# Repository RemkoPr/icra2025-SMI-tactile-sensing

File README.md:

# ICRA2025: Self-Mixing Laser Interferometry for Robotic Tactile Sensing

[[Main Paper](https://arxiv.org/abs/2502.15390), [Follow-up](https://arxiv.org/abs/2504.13711)] The source files in this repo are provided as-is, additional support for recreating the design can be requested, see contact information below.

# Repo structure

`code > arduino` contains readout firmware for the fingertips. In the paper, the SMI fingertip was read by an Arduino UNO or our [Halberd coupling](https://github.com/RemkoPr/airo-halberd/tree/main), the microphone was read by an Arduino MKR 1000 WiFi.

`code > python` contains code to communicate with the readout microcontrollers from a remote machine over a serial connection.

`data` contains the data files used in the paper.

`mechanical-design` contains SolidWorks design files for the structural parts of the fingertips.

`pcb-design` contains KiCad design files for the PCBs.

For the spectrogram classificatier used in the [follow-up paper](https://arxiv.org/abs/2504.13711), see [this repo](https://github.com/tlpss/ast).

# User Guide

The info in this paragraph is relevant for both the microphone and the laser.

Order the PCBs (`pcb-design > microphone` and `pcb-design > laser`) from your favorite manufacturer, refer to the BOM in the main directory of this repo for required parts.
Print the .stl files in `mechanical-design`.
The process of moulding the silicone contact surface is illustrated by the graphic on the right. To keep the "sensor cavity insert" in the right position, fix it with hot glue. It is recommended to attach the "mounting interface" to the fingertip while curing, so that the silicone has less chance to leak.

<BR CLEAR="all">

## Microphone specifics

On the PCB, you must set the microphone to either by left or right channel, this will determine during which phase of the I2S communication cycle the microphone sends its data. Do this by soldering a bridge as indicated on the image (the readout code in this repo was tested for left channel, so with a bridge soldered from the middle pad to the L pad).

The MKR1000 firmware (`code > arduino > microphone`) was used for the paper, the wiring is explained in the top rows of the `I2S_MKR1000.ino` file. The `I2S_ArduinoNanoBLE_16kHz` is a first attempt at a readout implementation for the Arduino Nano 33 BLE, for which the standard I2S library isn't implemented.

To run the Python code (`code > python`), run `python -m code.python.communication.readers.micmanip_serial_reader`. The data is published to a CycloneDDS topic MicManip. You can visualise it using `python -m code.python.visualisation.visualisers.micmanip_spectrogram_visualiser MicManip`
<BR CLEAR="all">

## Laser specifics

⚠️ The SMI circuit has a ~5 min warmup time before microvibrations can be measured.

The readout frequency when read with an Arduino UNO was 3.7kHz, and 18kHz with our [Halberd coupling](https://github.com/RemkoPr/airo-halberd/tree/main) (or equivalently with an Arduino Nano 33 BLE, same microcontroller unit). When using higher readout frequency, turn off the 2kHz anti-aliasing filter with the on-PCB slide switch.

To run the Python code (`code > python`), run `python -m code.python.communication.readers.laserslip_serial_reader`. The data is published to a CycloneDDS topic LaserSlip. You can visualise it using `python -m code.python.visualisation.visualisers.laserslip_spectrogram_visualiser LaserSlip`

# Contact

For support regarding the design files in this repo, raise an issue or contact me at remko.proesmans@ugent.be.

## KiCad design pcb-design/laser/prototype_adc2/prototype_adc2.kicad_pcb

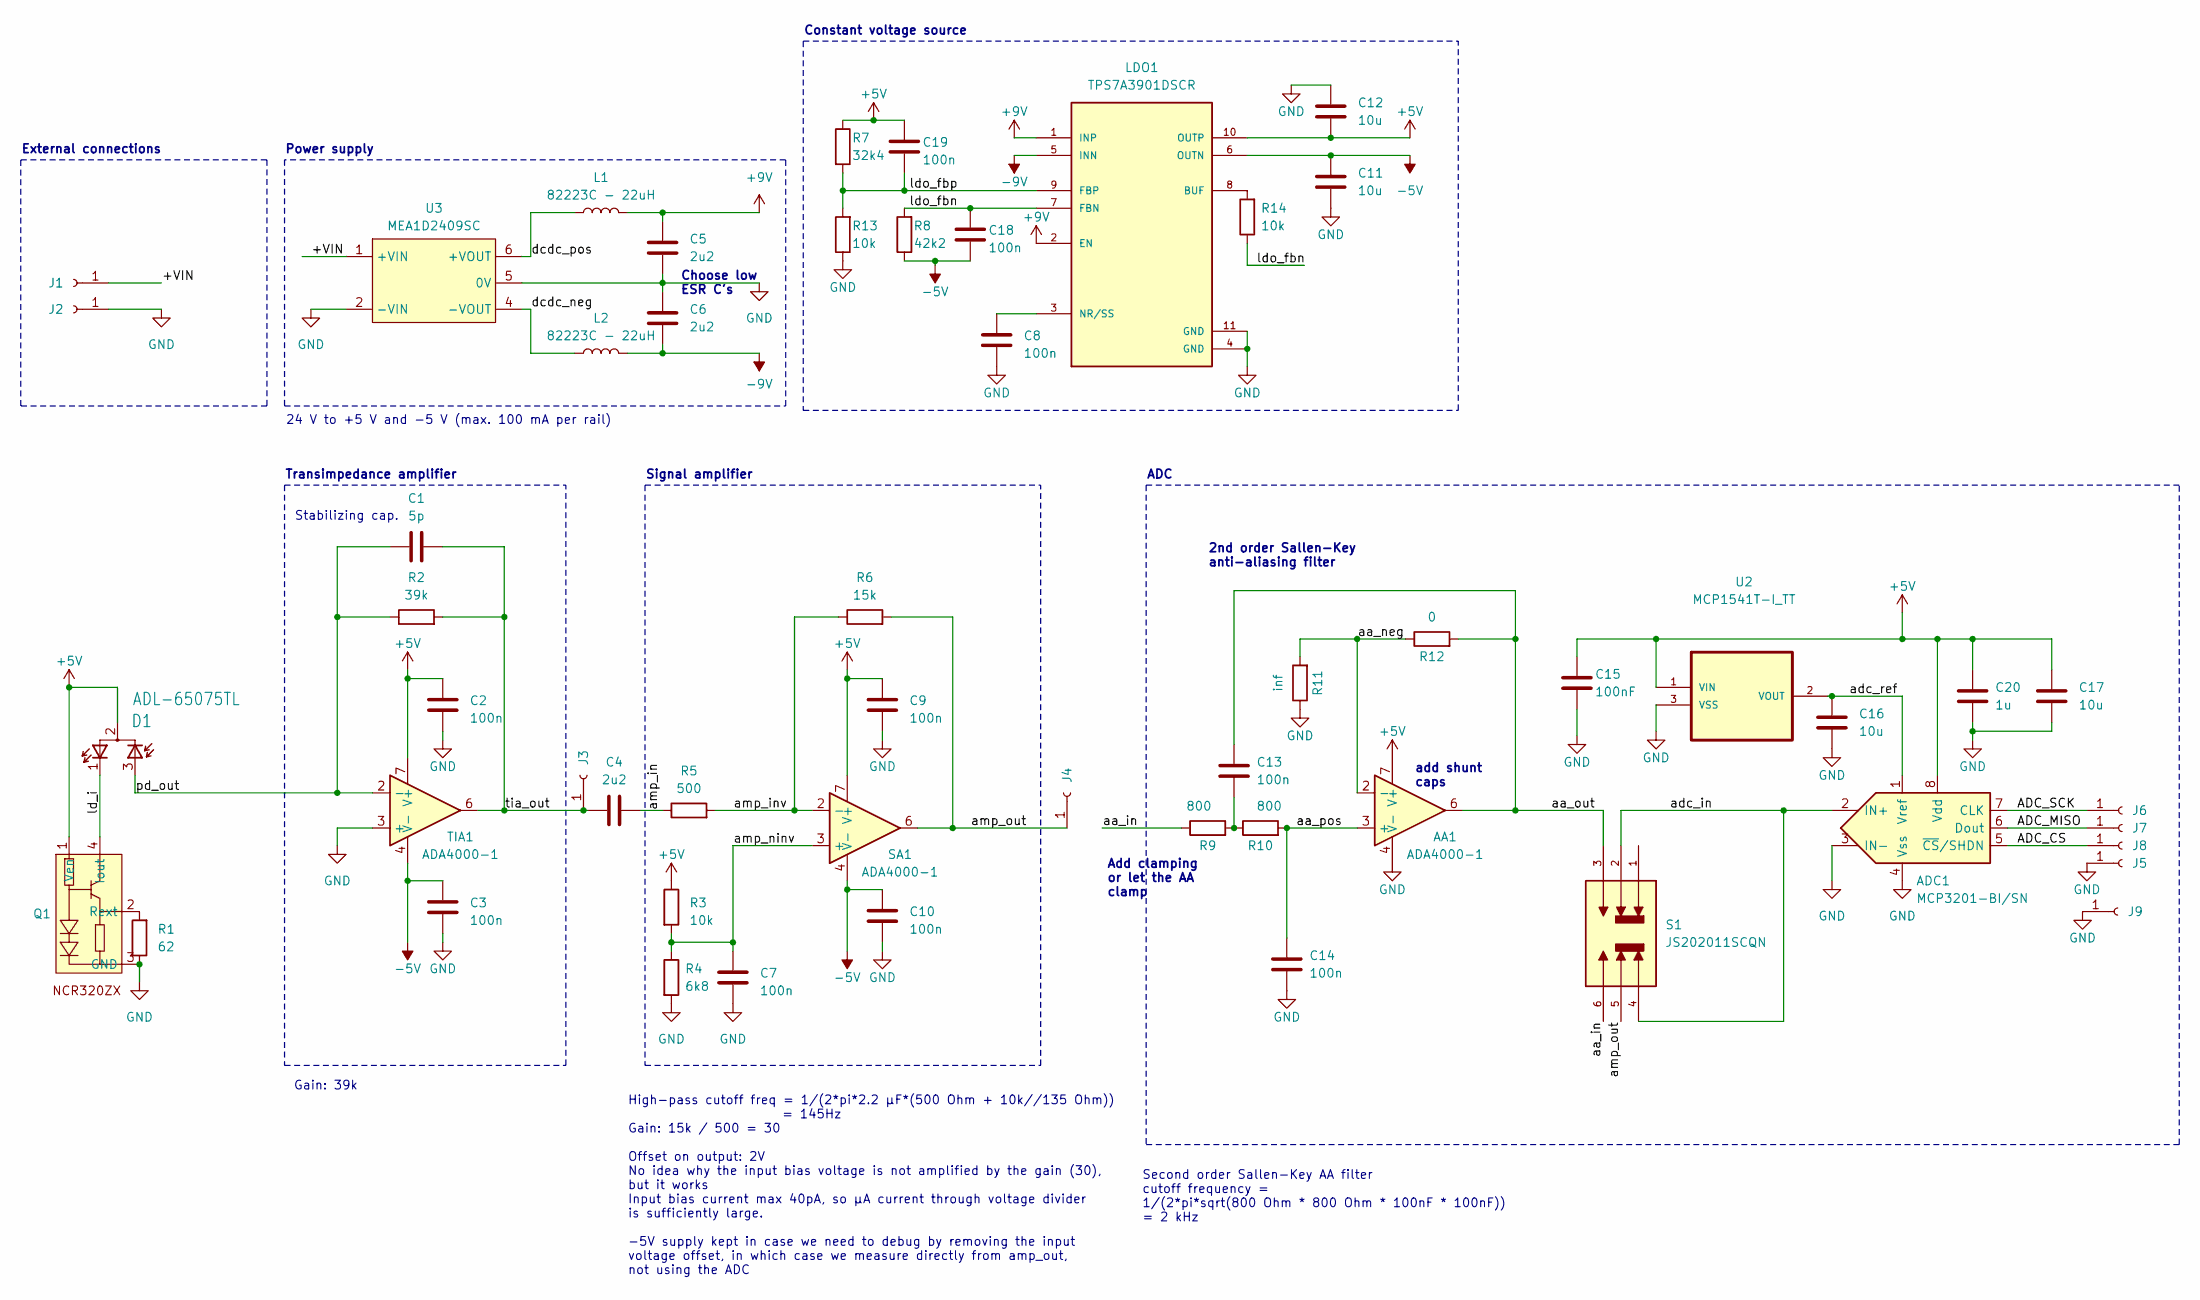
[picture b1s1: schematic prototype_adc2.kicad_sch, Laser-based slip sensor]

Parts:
AA1: ADA4000-1; ada4000-SOIC127P600X175-8N
ADC1: MCP3201-BI/SN; SOIC127P600X175-8N
C1: 5p; C_0603_1608Metric
C2, C3, C7, C8, C9, C10, C13, C14, C18, C19: 100n; C_0603_1608Metric
C4, C5, C6: 2u2; C_0603_1608Metric
C11, C12, C16, C17: 10u; C_0603_1608Metric
C15: 100nF; C_0603_1608Metric
C20: 1u; C_0603_1608Metric
D1: ADL-65075TL; TO18L
J1, J2, J3, J4, J5, J6, J7, J8, J9: Conn_01x01_Socket; HOLE
L1, L2: 82223C - 22uH; 8200
LDO1: TPS7A3901DSCR; SON50P300X300X80-11N
Q1: TRANS_BCP56-16TX
R1: 62; R_0603_1608Metric
R2: 39k; R_0603_1608Metric
R3, R13, R14: 10k; R_0603_1608Metric
R4: 6k8; R_0603_1608Metric
R5: 500; R_0603_1608Metric
R6: 15k; R_0603_1608Metric
R7: 32k4; R_0603_1608Metric
R8: 42k2; R_0603_1608Metric
R9, R10: 800; R_0603_1608Metric
R11: inf; R_0603_1608Metric
R12: 0; R_0603_1608Metric
S1: JS202011SCQN; SW_JS202011SCQN
SA1: ADA4000-1; ada4000-SOIC127P600X175-8N
TIA1: ADA4000-1; ada4000-SOIC127P600X175-8N
U2: MCP1541T-I_TT; SOT96P237X112-3N
U3: MEA1D2409SC

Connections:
+5V: AA1.7 (V+), ADC1.8 (Vdd), C2.1, C9.1, C12.2, C15.1, C17.1, C19.1, C20.1, D1.2 (CMONI), LDO1.10 (OUTP), Q1.1 (Ven), R3.1, R7.1, SA1.7 (V+), TIA1.7 (V+), U2.1 (VIN)
+9V: C5.1, L1.2, LDO1.1 (INP), LDO1.2 (EN)
-5V: C3.1, C10.1, C11.1, C18.2, LDO1.6 (OUTN), R8.1, SA1.4 (V-), TIA1.4 (V-)
-9V: C6.2, L2.2, LDO1.5 (INN)
/+VIN: J1.1, U3.1 (+VIN)
/ADC_CS: ADC1.5 (~CS/SHDN), J8.1
/ADC_MISO: ADC1.6 (Dout), J7.1
/ADC_SCK: ADC1.7 (CLK), J6.1
/aa_in: R9.1, S1.6
/aa_neg: AA1.2 (-), R11.2, R12.1
/aa_out: AA1.6, C13.1, R12.2, S1.3
/aa_pos: AA1.3 (+), C14.1, R10.2
/adc_in: ADC1.2 (IN+), S1.2, S1.4
/adc_ref: ADC1.1 (Vref), C16.1, U2.2 (VOUT)
/amp_in: C4.2, R5.1
/amp_inv: R5.2, R6.1, SA1.2 (-)
/amp_ninv: C7.1, R3.2, R4.1, SA1.3 (+)
/amp_out: J4.1, R6.2, S1.5, SA1.6
/dcdc_neg: L2.1, U3.4 (-VOUT)
/dcdc_pos: L1.1, U3.6 (+VOUT)
/ld_i: D1.1 (C), Q1.4 (Iout)
/ldo_fbn: C18.1, LDO1.7 (FBN), R8.2, R14.1
/ldo_fbp: C19.2, LDO1.9 (FBP), R7.2, R13.2
/pd_out: C1.1, D1.3 (A), R2.1, TIA1.2 (-)
/tia_out: C1.2, C4.1, J3.1, R2.2, TIA1.6
GND: AA1.4 (V-), ADC1.3 (IN-), ADC1.4 (Vss), C2.2, C3.2, C5.2, C6.1, C7.2, C8.2, C9.2, C10.2, C11.2, C12.1, C14.2, C15.2, C16.2, C17.2, C20.2, J2.1, J5.1, J9.1, LDO1.4 (GND), LDO1.11 (GND), Q1.3 (GND), R1.1, R4.2, R11.1, R13.1, TIA1.3 (+), U2.3 (VSS), U3.2 (-VIN), U3.5 (0V)
unnamed: C13.2, R9.2, R10.1
unnamed: LDO1.8 (BUF), R14.2
unnamed: C8.1, LDO1.3 (NR/SS)
unnamed: Q1.2 (Rext), R1.2

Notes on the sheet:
ADC
Add clamping or let the AA clamp
Second order Sallen-Key AA filter cutoff frequency = 1/(2*pi*sqrt(800 Ohm * 800 Ohm * 100nF * 100nF)) = 2 kHz
2nd order Sallen-Key anti-aliasing filter
High-pass cutoff freq = 1/(2*pi*2.2 µF*(500 Ohm + 10k//135 Ohm)) = 145Hz Gain: 15k / 500 = 30 Offset on output: 2V No idea why the input bias voltage is not amplified by the gain (30), but it works Input bias current max 40pA, so µA current through voltage divider is sufficiently large. -5V supply 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
Gain: 39k
24 V to +5 V and -5 V (max. 100 mA per rail)
Stabilizing cap.
External connections
Signal amplifier
Transimpedance amplifier
add shunt caps
Constant voltage source
Power supply
Choose low ESR C's

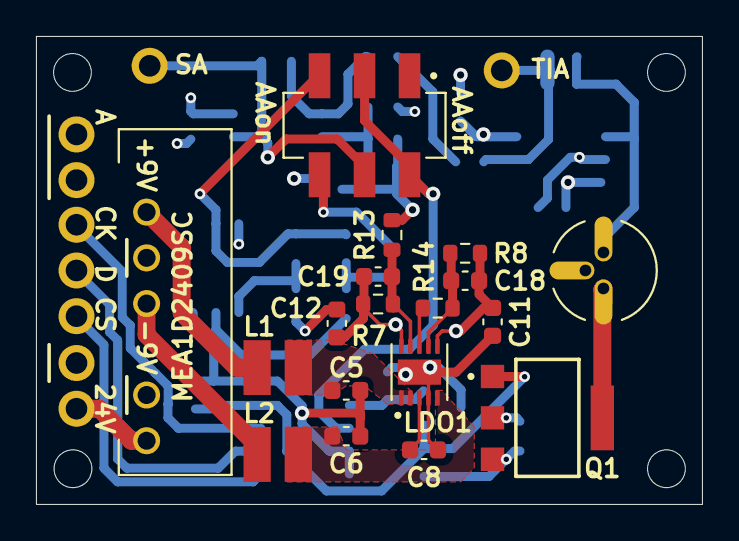
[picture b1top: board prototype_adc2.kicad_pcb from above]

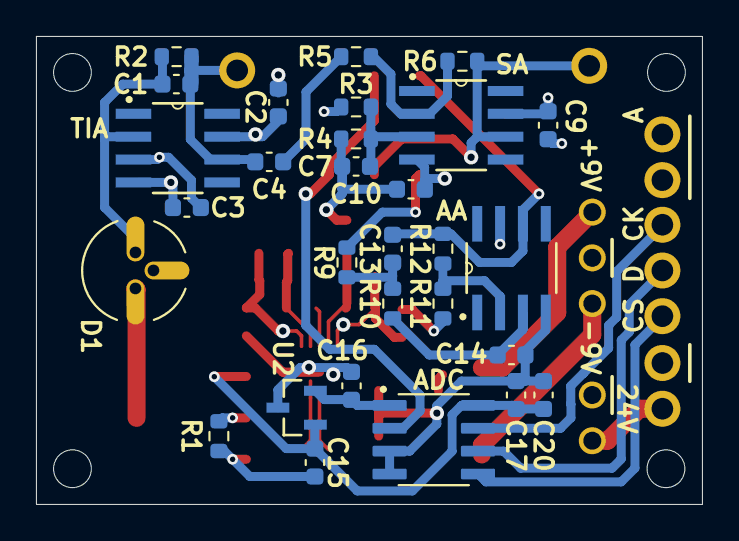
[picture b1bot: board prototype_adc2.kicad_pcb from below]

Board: 4 copper layers, 37.0 x 26.0 mm, 55 parts (29 on the bottom side), 30 nets.

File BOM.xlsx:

Mechanical | Qty per fingertip | Purpose
3D filament (e.g. PLA) |  | Mechanical parts
Castable Silicone 50A hardness (e.g. Silicone Addition colorless 50 by Silicone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 |  | Silicone contact surface
M3 threaded heat-set inserts | 2 | Inserted into the mounting interface
M5x14 bolt | 1 | Mounting fingertip to Robotiq gripper
M2x6 bolts | 4 | Attaching PCBs to printed fingertips
Electrical | Qty per fingertip | Item | PCB designation
Microphone
ICS43434 | 1 | Microphone
100 nF 0603 capacitor | 1
100 kOhm 0603 resistor | 1
Laser
ADL-65075TL | 1 | Laser | D1
ncr320zx | 1 | Constant current source | Q1
ADA4000-1 | 3 | Amplifiers and filters | TIA1, SA1, AA1
MCP3201-BI/SN | 1 | ADC | ADC1
MCP1541T-I_TT | 1 | ADC reference voltage | U2
JS202011SCQN | 1 | Switch | S1
TPS7A3901DSCR | 1 | Voltage regulator | LDO1
MEA1D2409SC | 1 | Voltage regulator | U3
82223C | 2 | 22 µH inductor | L1, L2
5 pF 0603 capacitor | 1 | TIA gain stabilising | C1
100 nF 0603 capacitor | 10 |  | C2, C3, C7, C8, C9, C10, C13, C14, C15, C19
1 µF 0603 capacitor | 1 |  | C20
2,2 µF 0603 capacitor | 3 |  | C4, C5, C6
10 µF 0603 capacitor | 4 |  | C11, C12, C16, C17
500 Ohm 0603 resistor | 1 |  | R5
800 Ohm 0603 resistor | 2 |  | R9, R10
6,8 kOhm 0603 resistor | 1 |  | R4
10 kOhm 0603 resistor | 3 |  | R3, R13, R14
15 kOhm 0603 resistor | 1 |  | R6
32,4 kOhm 0603 resistor | 1 |  | R7
39 kOhm 0603 resistor | 1 | TIA gain | R2
42,2 kOhm 0603 resistor | 1 |  | R8

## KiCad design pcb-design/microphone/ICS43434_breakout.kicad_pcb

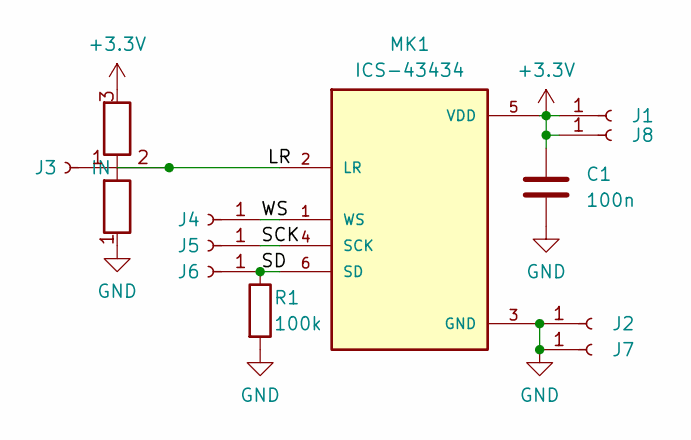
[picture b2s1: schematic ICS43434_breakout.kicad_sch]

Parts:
C1: 100n; C_0603_1608Metric
J1, J2, J3, J4, J5, J6, J7, J8: Conn_01x01_Socket; HOLE
MK1: ICS-43434; MIC_ICS-43434
R1: 100k; R_0603_1608Metric
U1: ADDR_SELECT

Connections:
+3.3V: C1.1, J1.1, J8.1, MK1.5 (VDD), U1.3; also elsewhere on the board
/LR: J3.1, MK1.2 (LR), U1.2 (IN); also elsewhere on the board
/SCK: J5.1, MK1.4 (SCK); also elsewhere on the board
/SD: J6.1, MK1.6 (SD), R1.1; also elsewhere on the board
/WS: J4.1, MK1.1 (WS); also elsewhere on the board
GND: C1.2, J2.1, J7.1, MK1.3 (GND), R1.2, U1.1; also elsewhere on the board

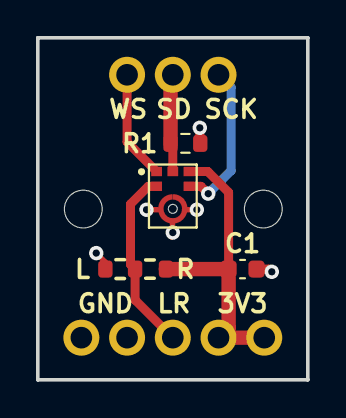
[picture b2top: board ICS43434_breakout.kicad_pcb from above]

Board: 2 copper layers, 15.0 x 19.0 mm, 12 parts (0 on the bottom side), 6 nets.

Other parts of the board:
ICS-43434: ICS-43434; MIC_ICS-43434

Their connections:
+3.3V: ICS-43434.5 (VDD); also elsewhere on the board
/LR: ICS-43434.2 (LR); also elsewhere on the board
/SCK: ICS-43434.4 (SCK); also elsewhere on the board
/SD: ICS-43434.6 (SD); also elsewhere on the board
/WS: ICS-43434.1 (WS); also elsewhere on the board
GND: ICS-43434.3 (GND); also elsewhere on the board

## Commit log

2024-09-09 inital push
2025-02-19 added motor noise data files and plotting notebook
2025-02-27 structure plotting notebook better
2025-02-27 added stepper motor plot to notebook
2025-02-27 added cup plots to notebook
2025-03-03 notebook update
2025-03-04 plotting notebook update
2025-03-17 removed legacy microphone readout code
2025-03-17 updated MKR1000 mic readout code
2025-03-17 renamed mechanical cad files to align with moulding image
2025-03-17 laser schematic AA cutoff fix
2025-03-17 added BOM
2025-03-17 fixed laser footprint on pcb
2025-03-17 added python readout and viz code
